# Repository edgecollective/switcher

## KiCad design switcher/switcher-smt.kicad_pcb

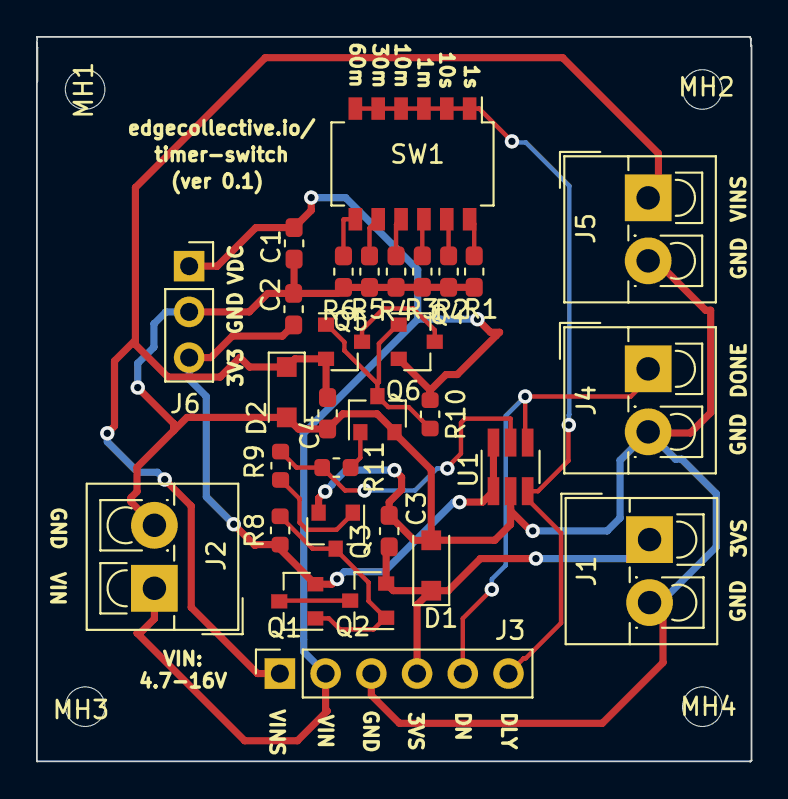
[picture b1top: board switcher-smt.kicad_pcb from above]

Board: 2 copper layers, 39.7 x 40.3 mm, 34 parts (0 on the bottom side), 20 nets.

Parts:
C1, C2, C3, C4: CP; C_0603_1608Metric_Pad1.05x0.95mm_HandSolder
D1, D2: D; D_SOD-123F
J1, J2, J4, J5: Screw_Terminal_01x02; TerminalBlock_4Ucon_1x02_P3.50mm_Vertical
J3: Conn_01x06_Female; PinSocket_1x06_P2.54mm_Vertical
J6: sreg; PinSocket_1x03_P2.54mm_Vertical
MH1, MH2, MH3, MH4: MountingHole; MountingHole_2.2mm_M2
Q1, Q2, Q4, Q5: DMP2045U; SOT-23
Q3, Q6: MMBT3904; SOT-23
R1: RD1; R_0603_1608Metric_Pad1.05x0.95mm_HandSolder
R2: RD2; R_0603_1608Metric_Pad1.05x0.95mm_HandSolder
R3: RD3; R_0603_1608Metric_Pad1.05x0.95mm_HandSolder
R4: RD4; R_0603_1608Metric_Pad1.05x0.95mm_HandSolder
R5: RD5; R_0603_1608Metric_Pad1.05x0.95mm_HandSolder
R6: RD6; R_0603_1608Metric_Pad1.05x0.95mm_HandSolder
R8, R10: 10K; R_0603_1608Metric
R9, R11: 100K; R_0603_1608Metric
SW1: omron-a6h; SW_DIP_SPSTx06_Slide_Omron_A6H-6101_W6.15mm_P1.27mm
U1: tpl5110; SOT-23-6_Handsoldering

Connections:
3V3-SWITCH: C3.1, D1.1, J1.1, J3.4, Q2.2
+3V3: C2.1, J6.3, Q1.2, R8.1, U1.1, U1.6
+VDC: C1.1, J2.1, J3.2, J6.1, Q4.2, R10.1
DELAY: J3.6, SW1.1, SW1.2, SW1.3, SW1.4, SW1.5, SW1.6, U1.3
DONE: J3.5, J4.1, U1.4
GND: C1.2, C2.2, C3.2, C4.2, D1.2, D2.2, J1.2, J2.2, J3.3, J4.2, J5.2, J6.2, Q3.2, Q6.2, R1.1, R2.1, R3.1, R4.1, R5.1, R6.1, U1.2
unnamed: Q1.1, Q2.1, Q3.3, R8.2
unnamed: Q1.3, Q2.3
unnamed: Q3.1, R9.2
unnamed: Q4.1, Q5.1, Q6.3, R10.2
unnamed: Q4.3, Q5.3
unnamed: Q6.1, R11.2
unnamed: R1.2, SW1.12
unnamed: R2.2, SW1.11
unnamed: R3.2, SW1.10
unnamed: R4.2, SW1.9
unnamed: R5.2, SW1.8
unnamed: R6.2, SW1.7
SWITCHER: R9.1, R11.1, U1.5
VDD-SWITCH: C4.1, D2.1, J3.1, J5.1, Q5.2

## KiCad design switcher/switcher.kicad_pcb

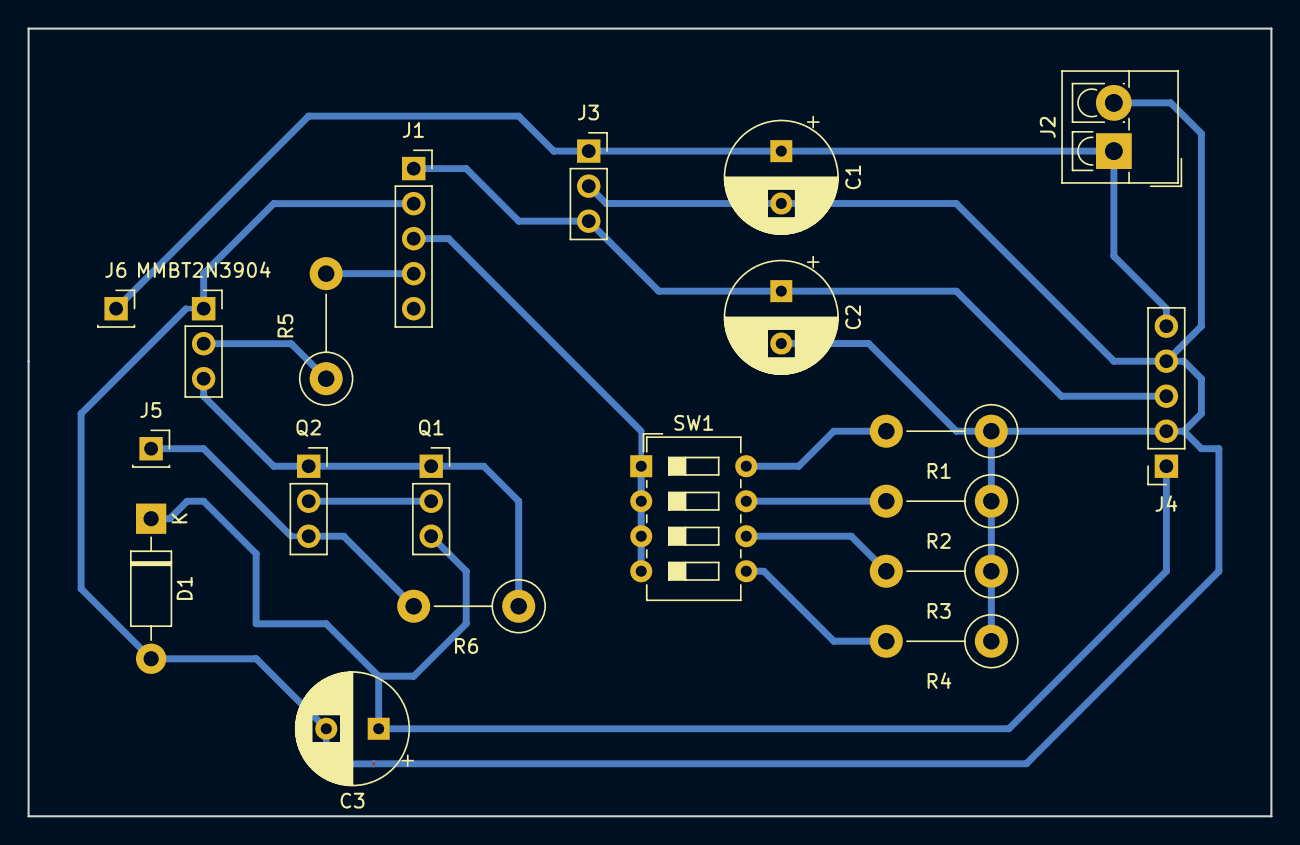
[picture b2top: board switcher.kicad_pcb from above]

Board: 2 copper layers, 90.2 x 57.2 mm, 20 parts (0 on the bottom side), 13 nets.

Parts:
C1, C2, C3: CP; CP_Radial_D8.0mm_P3.80mm
D1: D; D_DO-41_SOD81_P10.16mm_Horizontal
J1: ADA_TPL5100; PinSocket_1x05_P2.54mm_Vertical
J2: Screw_Terminal_01x02; TerminalBlock_4Ucon_1x02_P3.50mm_Vertical
J3: sreg; PinSocket_1x03_P2.54mm_Vertical
J4: Conn_01x05_Female; PinSocket_1x05_P2.54mm_Vertical
J5, J6: Conn_01x01_Female; PinSocket_1x01_P2.54mm_Vertical
MMBT2N3904: Q_NPN_EBC; PinSocket_1x03_P2.54mm_Vertical
Q1, Q2: DMP2045U; PinSocket_1x03_P2.54mm_Vertical
R1: RD1; R_Axial_DIN0411_L9.9mm_D3.6mm_P7.62mm_Vertical
R2: RD2; R_Axial_DIN0411_L9.9mm_D3.6mm_P7.62mm_Vertical
R3: RD3; R_Axial_DIN0411_L9.9mm_D3.6mm_P7.62mm_Vertical
R4: RD4; R_Axial_DIN0411_L9.9mm_D3.6mm_P7.62mm_Vertical
R5: 100K; R_Axial_DIN0411_L9.9mm_D3.6mm_P7.62mm_Vertical
R6: 10K; R_Axial_DIN0411_L9.9mm_D3.6mm_P7.62mm_Vertical
SW1: SW_DIP_x04; SW_DIP_SPSTx04_Slide_6.7x11.72mm_W7.62mm_P2.54mm_LowProfile

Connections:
+3V3: C2.1, J1.1, J3.3, J4.3
+VDC: C1.1, J2.1, J3.1, J4.5, J5.1, J6.1, Q2.3, R6.2
GND: C1.2, C2.2, C3.2, D1.2, J1.2, J2.2, J3.2, J4.2, J4.4, MMBT2N3904.1, R1.1, R2.1, R3.1, R4.1
unnamed: J1.3, SW1.1, SW1.2, SW1.3, SW1.4
unnamed: J1.4, R5.2
unnamed: MMBT2N3904.2, R5.1
unnamed: MMBT2N3904.3, Q1.1, Q2.1, R6.1
unnamed: Q1.2, Q2.2
unnamed: R1.2, SW1.8
unnamed: R2.2, SW1.7
unnamed: R3.2, SW1.6
unnamed: R4.2, SW1.5
VDD-SWITCH: C3.1, D1.1, J4.1, Q1.3
